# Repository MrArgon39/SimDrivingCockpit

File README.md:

# SimDrivingCockpit
All the code and other assorted stuff for this project

Folder Explanation
<ul>
  <li>Code - All of the code that I have made and will make.</li>
  <li>Reference Images - Mainly used for the steering wheel design.</li>
  <li>Make Physical Things - Where laser files and 3D? printing files will go. Same with PCBs.</li>
<li>Service Documentation - All of the docs about what wire I need to put where to get things to work.</li>
</ul>
Everything contained within the service documentation folder has not been created by me, and belongs to Lexus/Toyota.

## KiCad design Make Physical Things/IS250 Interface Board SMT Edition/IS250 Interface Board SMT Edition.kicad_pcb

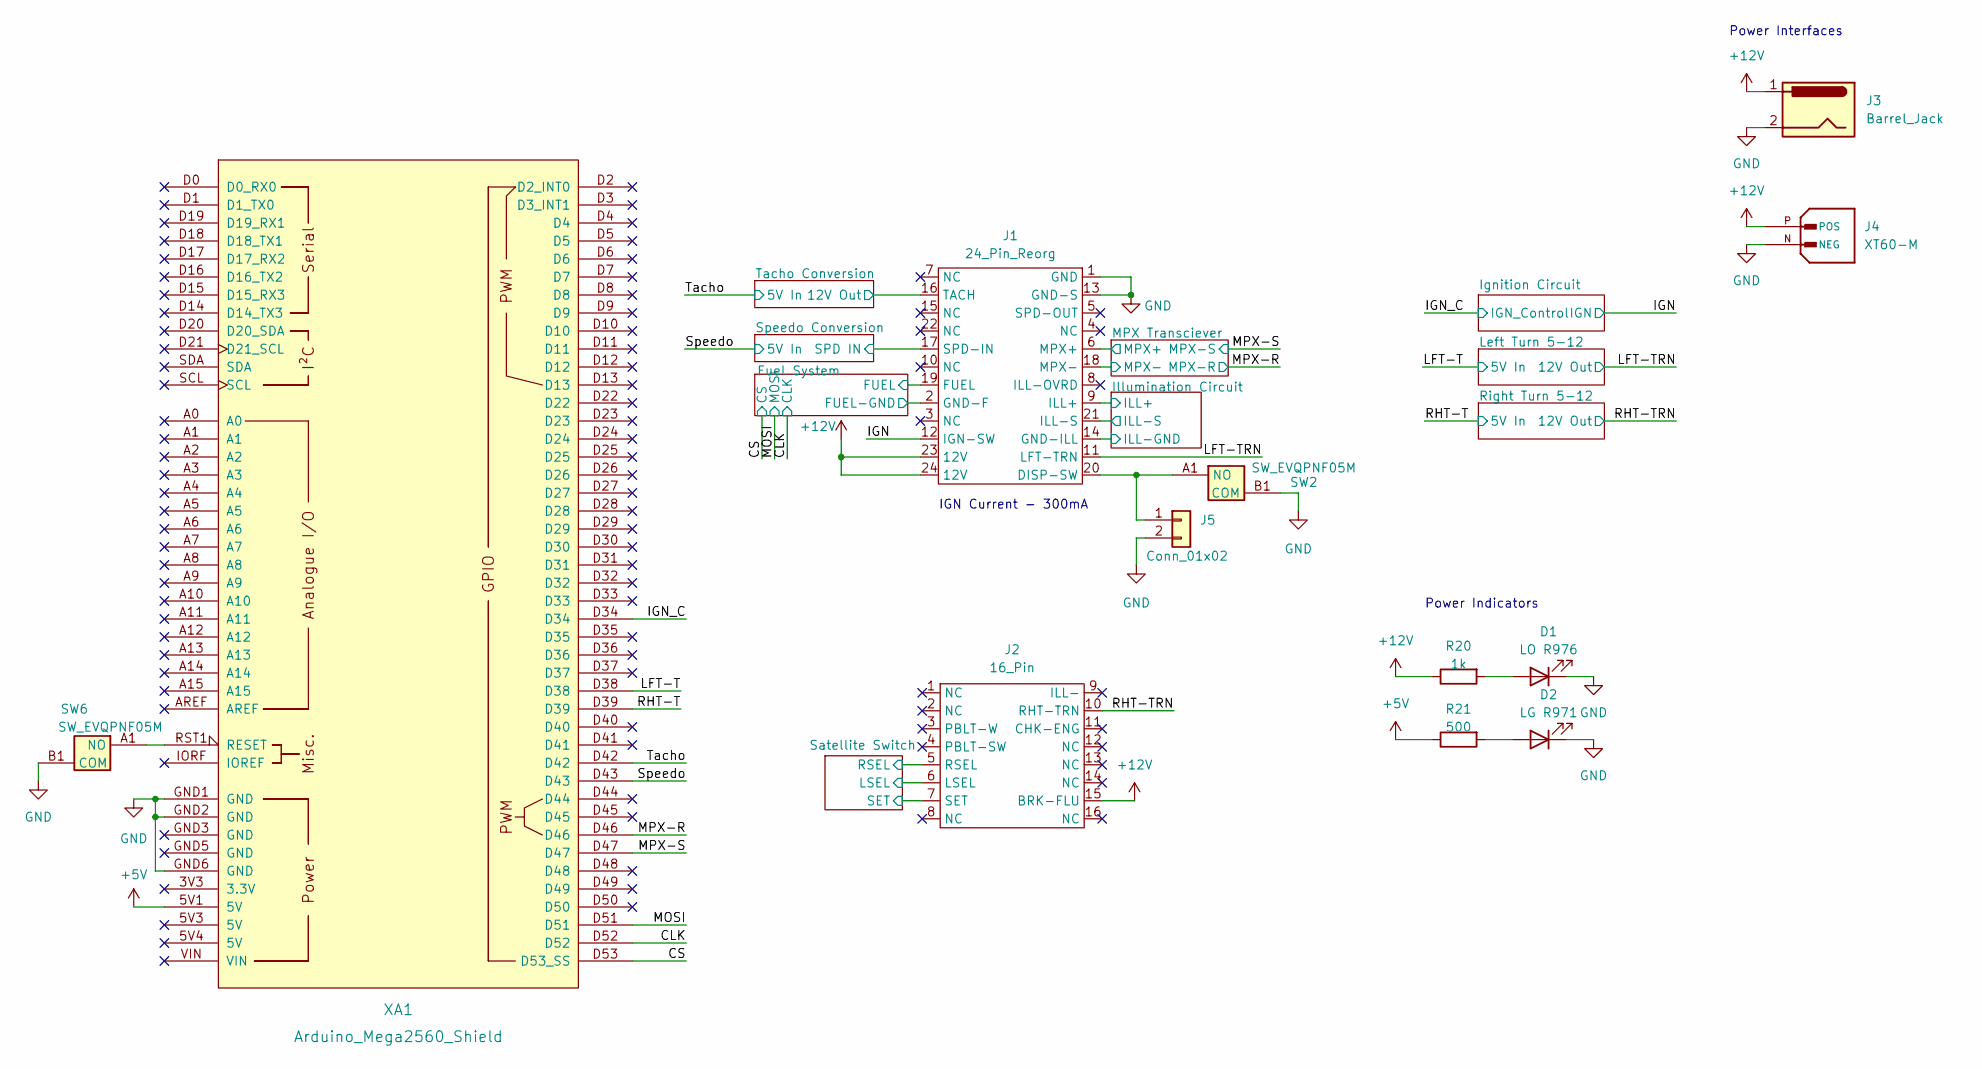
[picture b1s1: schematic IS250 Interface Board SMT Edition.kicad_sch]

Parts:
D1: LO R976; LEDC2012X90N
D2: LG R971; LEDC2012X90N
J1: 24_Pin_Reorg; 24Pin
J2: 16_Pin; 16Pin
J3: Barrel_Jack; BarrelJack_Horizontal
J4: XT60-M; AMASS_XT60-M; PARTREV V1.2
J5: Conn_01x02; PinHeader_1x02_P2.54mm_Vertical
R20: 1k; R_0805_2012Metric_Pad1.20x1.40mm_HandSolder
R21: 500; R_0805_2012Metric_Pad1.20x1.40mm_HandSolder
SW2, SW6: SW_EVQPNF05M; EVQPNF05M; Mouser Part Number 667-EVQ-PNF05M
XA1: Arduino_Mega2560_Shield

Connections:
+5V: R21.1, XA1.5V1 (5V); also elsewhere on the board
/CLK: XA1.D52; also elsewhere on the board
/CS: XA1.D53 (D53_SS); also elsewhere on the board
/Fuel System/FUEL: J1.19 (FUEL); also elsewhere on the board
/Fuel System/FUEL-GND: J1.2 (GND-F); also elsewhere on the board
/IGN: J1.12 (IGN-SW); also elsewhere on the board
/IGN_C: XA1.D34; also elsewhere on the board
/Illumination Circuit/ILL+: J1.9 (ILL+); also elsewhere on the board
/Illumination Circuit/ILL-GND: J1.14 (GND-ILL); also elsewhere on the board
/Illumination Circuit/ILL-S: J1.21 (ILL-S); also elsewhere on the board
/LFT-T: XA1.D38; also elsewhere on the board
/LFT-TRN: J1.11 (LFT-TRN); also elsewhere on the board
/MOSI: XA1.D51; also elsewhere on the board
/MPX Transciever/MPX+: J1.6 (MPX+); also elsewhere on the board
/MPX Transciever/MPX-: J1.18 (MPX-); also elsewhere on the board
/MPX-R: XA1.D46; also elsewhere on the board
/MPX-S: XA1.D47; also elsewhere on the board
/RHT-T: XA1.D39; also elsewhere on the board
/RHT-TRN: J2.10 (RHT-TRN); also elsewhere on the board
/Satellite Switch/LSEL: J2.6 (LSEL); also elsewhere on the board
/Satellite Switch/RSEL: J2.5 (RSEL); also elsewhere on the board
/Satellite Switch/SET: J2.7 (SET); also elsewhere on the board
/Speedo: XA1.D43; also elsewhere on the board
/Speedo Conversion/SPD IN: J1.17 (SPD-IN); also elsewhere on the board
/Tacho Conversion/12V Out: J1.16 (TACH); also elsewhere on the board
GND: D1.1 (K), D2.1 (K), J1.1 (GND), J1.13 (GND-S), J3.2, J4.N (NEG), J5.2, SW2.B1 (COM), SW6.B1 (COM), XA1.GND1 (GND), XA1.GND2 (GND), XA1.GND6 (GND); also elsewhere on the board
unnamed: D1.2 (A), R20.2
unnamed: D2.2 (A), R21.2
unnamed: J1.20 (DISP-SW), J5.1, SW2.A1 (NO)
unnamed 47: SW6.A1 (NO), XA1.RST1 (RESET); also elsewhere on the board

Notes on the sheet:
IGN Current - 300mA
Power Interfaces
Power Indicators

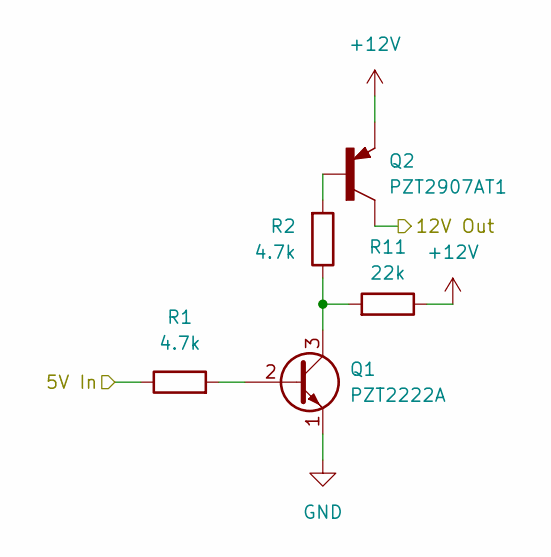
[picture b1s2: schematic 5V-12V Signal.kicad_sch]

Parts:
Q1: PZT2222A; SOT-223
Q2: PZT2907AT1; SOT-223
R1, R2: 4.7k; R_0805_2012Metric_Pad1.20x1.40mm_HandSolder
R11: 22k; R_0805_2012Metric_Pad1.20x1.40mm_HandSolder

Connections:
/Tacho Conversion/12V Out: Q2.3 (C); also elsewhere on the board
GND: Q1.1 (E); also elsewhere on the board
unnamed: Q1.2 (B), R1.2
unnamed: Q2.2 (B), R2.2

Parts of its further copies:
Q8, Q10: PZT2222A; SOT-223
Q9, Q11: PZT2907AT1; SOT-223
R13, R14, R16, R17: 4.7k; R_0805_2012Metric_Pad1.20x1.40mm_HandSolder
R15, R18: 22k; R_0805_2012Metric_Pad1.20x1.40mm_HandSolder

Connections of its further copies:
/LFT-T: R13.1; also elsewhere on the board
/LFT-TRN: Q9.3 (C); also elsewhere on the board
/RHT-T: R16.1; also elsewhere on the board
/RHT-TRN: Q11.3 (C); also elsewhere on the board
GND: Q8.1 (E), Q10.1 (E); also elsewhere on the board
unnamed: Q8.2 (B), R13.2
unnamed: Q8.3 (C), R14.1, R15.2
unnamed: Q9.2 (B), R14.2
unnamed: Q10.2 (B), R16.2
unnamed: Q10.3 (C), R17.1, R18.2
unnamed: Q11.2 (B), R17.2

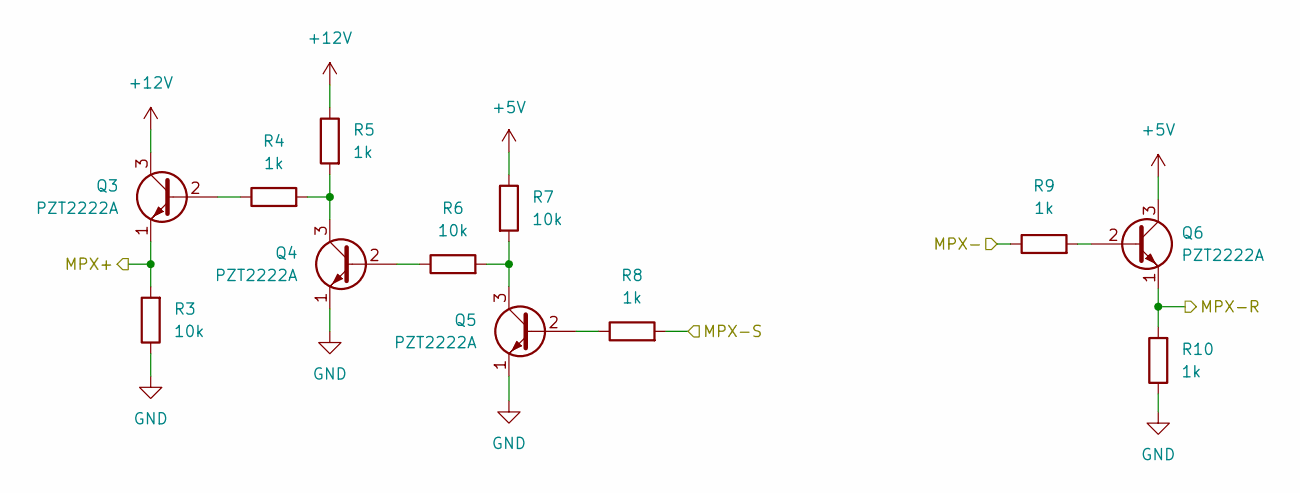
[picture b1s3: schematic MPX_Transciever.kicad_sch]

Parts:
Q3, Q4, Q5, Q6: PZT2222A; SOT-223
R3, R6, R7: 10k; R_0805_2012Metric_Pad1.20x1.40mm_HandSolder
R4, R5, R8, R9, R10: 1k; R_0805_2012Metric_Pad1.20x1.40mm_HandSolder

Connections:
+5V: Q6.3 (C), R7.1; also elsewhere on the board
/MPX Transciever/MPX+: Q3.1 (E), R3.2; also elsewhere on the board
/MPX Transciever/MPX-: R9.1; also elsewhere on the board
/MPX-R: Q6.1 (E), R10.2; also elsewhere on the board
/MPX-S: R8.2; also elsewhere on the board
GND: Q4.1 (E), Q5.1 (E), R3.1, R10.1; also elsewhere on the board
unnamed: Q3.2 (B), R4.1
unnamed: Q4.2 (B), R6.1
unnamed: Q4.3 (C), R4.2, R5.2
unnamed: Q5.2 (B), R8.1
unnamed: Q5.3 (C), R6.2, R7.2
unnamed: Q6.2 (B), R9.2

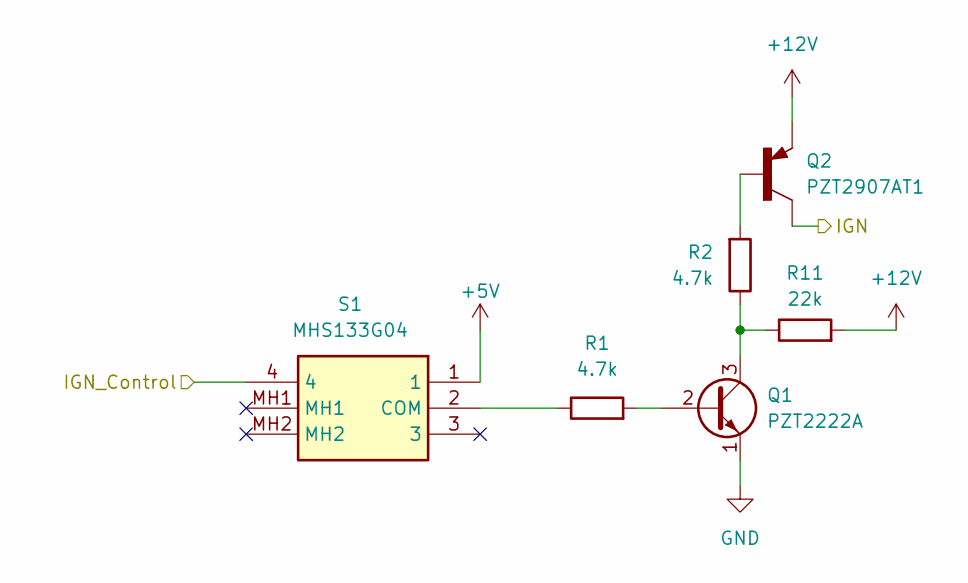
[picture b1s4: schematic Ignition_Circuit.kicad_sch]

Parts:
Q1: PZT2222A; SOT-223
Q2: PZT2907AT1; SOT-223
R1, R2: 4.7k; R_0805_2012Metric_Pad1.20x1.40mm_HandSolder
R11: 22k; R_0805_2012Metric_Pad1.20x1.40mm_HandSolder
S1: MHS133G04; Mouser Part Number 506-MHS133G04

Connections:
+5V: S1.1; also elsewhere on the board
/IGN_C: S1.4; also elsewhere on the board
/Tacho Conversion/12V Out: Q2.3 (C); also elsewhere on the board
GND: Q1.1 (E); also elsewhere on the board
unnamed: Q1.2 (B), R1.2
unnamed: Q2.2 (B), R2.2

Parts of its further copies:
Q8, Q10, Q12: PZT2222A; SOT-223
Q9, Q11, Q13: PZT2907AT1; SOT-223
R13, R14, R16, R17, R22, R23: 4.7k; R_0805_2012Metric_Pad1.20x1.40mm_HandSolder
R15, R18, R24: 22k; R_0805_2012Metric_Pad1.20x1.40mm_HandSolder

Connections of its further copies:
/IGN: Q13.3 (C); also elsewhere on the board
/LFT-T: R13.1; also elsewhere on the board
/LFT-TRN: Q9.3 (C); also elsewhere on the board
/RHT-T: R16.1; also elsewhere on the board
/RHT-TRN: Q11.3 (C); also elsewhere on the board
GND: Q8.1 (E), Q10.1 (E), Q12.1 (E); also elsewhere on the board
unnamed: Q8.2 (B), R13.2
unnamed: Q8.3 (C), R14.1, R15.2
unnamed: Q9.2 (B), R14.2
unnamed: Q10.2 (B), R16.2
unnamed: Q10.3 (C), R17.1, R18.2
unnamed: Q11.2 (B), R17.2
unnamed: Q12.2 (B), R22.2
unnamed: Q12.3 (C), R23.1, R24.1
unnamed: Q13.2 (B), R23.2

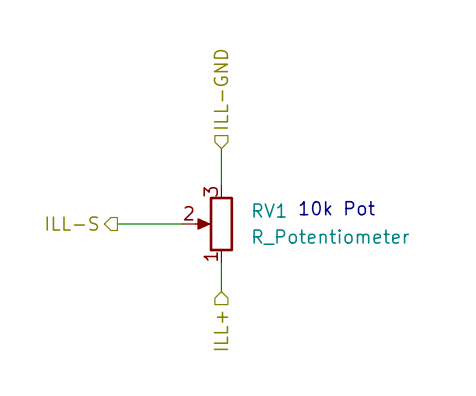
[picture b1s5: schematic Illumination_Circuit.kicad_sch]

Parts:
RV1: R_Potentiometer; Potentiometer_Bourns_3386P_Vertical

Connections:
/Illumination Circuit/ILL+: RV1.1; also elsewhere on the board
/Illumination Circuit/ILL-GND: RV1.3; also elsewhere on the board
/Illumination Circuit/ILL-S: RV1.2; also elsewhere on the board

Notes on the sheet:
10k Pot

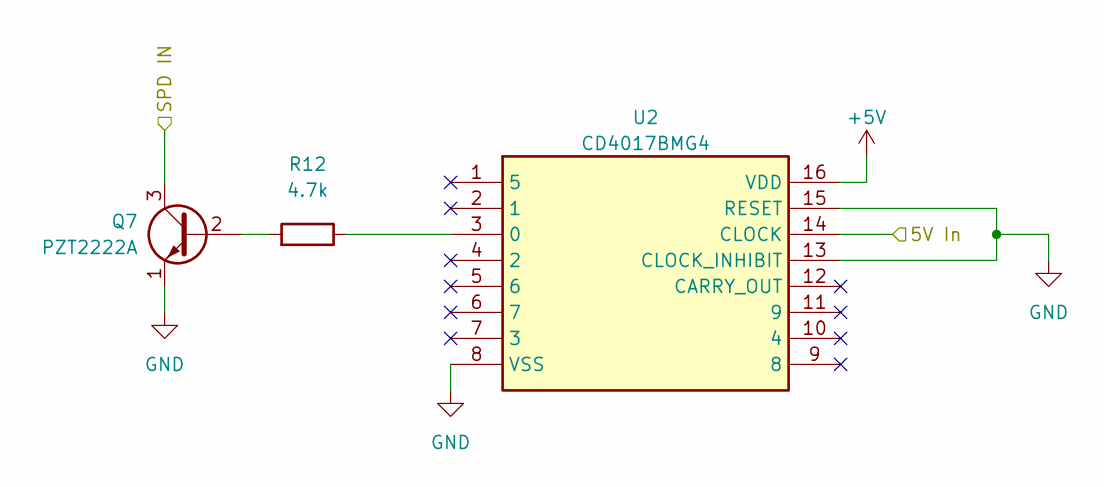
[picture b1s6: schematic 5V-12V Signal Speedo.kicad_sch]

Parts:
Q7: PZT2222A; SOT-223
R12: 4.7k; R_0805_2012Metric_Pad1.20x1.40mm_HandSolder
U2: CD4017BMG4; SOIC127P600X175-16N; Mouser Part Number 595-CD4017BMG4

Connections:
+5V: U2.16 (VDD); also elsewhere on the board
/Speedo: U2.14 (CLOCK); also elsewhere on the board
/Speedo Conversion/SPD IN: Q7.3 (C); also elsewhere on the board
GND: Q7.1 (E), U2.8 (VSS), U2.13 (CLOCK_INHIBIT), U2.15 (RESET); also elsewhere on the board
unnamed: Q7.2 (B), R12.2
unnamed: R12.1, U2.3 (0)

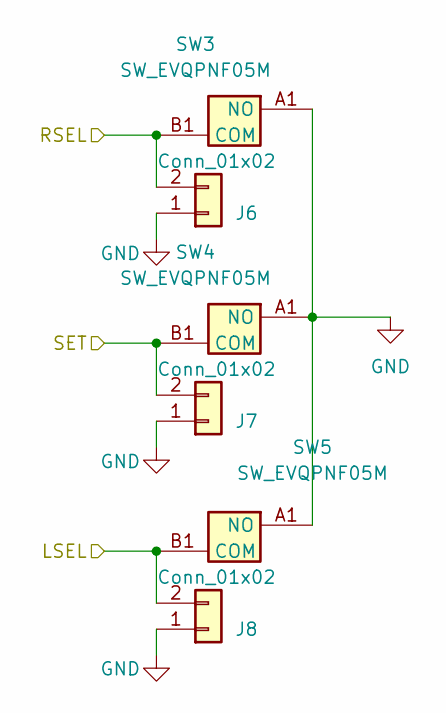
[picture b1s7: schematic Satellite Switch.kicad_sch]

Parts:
J6, J7, J8: Conn_01x02; PinHeader_1x02_P2.54mm_Vertical
SW3, SW4, SW5: SW_EVQPNF05M; EVQPNF05M; Mouser Part Number 667-EVQ-PNF05M

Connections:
/Satellite Switch/LSEL: J8.2, SW5.B1 (COM); also elsewhere on the board
/Satellite Switch/RSEL: J6.2, SW3.B1 (COM); also elsewhere on the board
/Satellite Switch/SET: J7.2, SW4.B1 (COM); also elsewhere on the board
GND: J6.1, J7.1, J8.1, SW3.A1 (NO), SW4.A1 (NO), SW5.A1 (NO); also elsewhere on the board

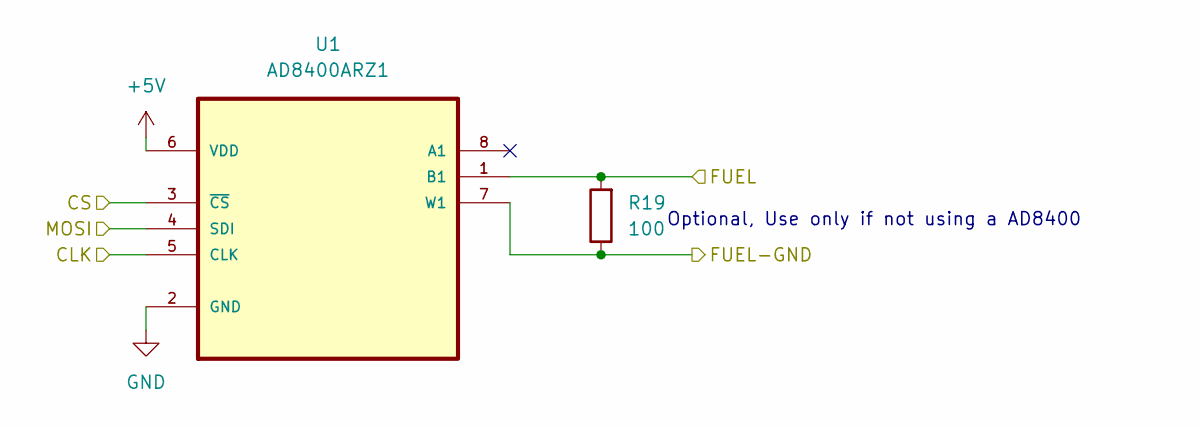
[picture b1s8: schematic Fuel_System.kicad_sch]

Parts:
R19: 100; R_0805_2012Metric_Pad1.20x1.40mm_HandSolder
U1: AD8400ARZ1; SO-8_3.9x4.9mm_P1.27mm; MPN AD8400ARZ1

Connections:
+5V: U1.6 (VDD); also elsewhere on the board
/CLK: U1.5 (CLK); also elsewhere on the board
/CS: U1.3 (~CS); also elsewhere on the board
/Fuel System/FUEL: R19.2, U1.1 (B1); also elsewhere on the board
/Fuel System/FUEL-GND: R19.1, U1.7 (W1); also elsewhere on the board
/MOSI: U1.4 (SDI); also elsewhere on the board
GND: U1.2 (GND); also elsewhere on the board

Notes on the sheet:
Optional, Use only if not using a AD8400

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
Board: 2 copper layers, 57 parts (12 on the bottom side), 53 nets, no tracks yet.

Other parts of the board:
locked: SW_EVQPNF05M; EVQPNF05M

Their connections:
GND: locked.B1 (COM); also elsewhere on the board
unnamed 47: locked.A1 (NO); also elsewhere on the board

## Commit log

2022-09-04 Added fundamental things to the repo
    Added all of my code up to this point, as well as the reference that I am using for the physical wheel.
    The pertinent parts of the service documentation have also been added for easy reference.
2022-09-04 Changed file locations
2022-09-05 Added the rest of the D-Pad controls for the wheel
2022-09-05 Added Cruise Control Buttons
2022-09-05 Added pedals, changed designators, moved buttons
2022-09-07 Added test code for the Speedometer, which works
2022-09-07 Edited Speed Test to work with SimHub
2022-09-08 Copied SHCP, Working Speedo Prototype
2022-09-08 gitignore broken
2022-09-08 Added the modified version of the BeanMPX lib
2022-09-08 Added BeanMPX library modified to use Timer3
2022-09-08 Experimented with speed, will rewrite for a 4017IC
2022-09-08 Majority of MPX Communications work
2022-09-11 Add the test code for the fuel gauge
    Added test code to implement the AD8400 digipot to control the fuel gauge
2022-09-11 Adapted fuel code to test on a Mega
2022-09-11 Added fuel code, and redid light and cruise code
2022-09-15 Updated Pedals to work correctly
2022-09-16 Implemented temp gauge, and added cruise speed
2022-09-17 Implemented cruise speed properly
2022-09-19 Redid HID reports to reduce report numbers
2022-09-20 Added Turn Signals
2022-09-23 Changed button check to allow multiple at once
2022-09-23 Added Paddles and missing back button
2022-10-20 Added Schematic
    Added the KiCAD Schematic for the Interface board
2022-10-20 Added Plate Detection Functionality
    Added the ability for the Pico to detect which faceplate is installed, and adjust the calibration accordingly
2022-10-20 Updated Components to have footprints
    Added footprints to components that had the wrong ones or were completely missing
2022-10-24 Added components to PCB
    Got all the components adding onto the PCB, and fixed pinname errors with the 2907
2022-10-24 Added XT60 and backup fuel resistor
    Added an XT60 power connector, and an optional resistor if there isn't an AD8400 connected, so that the fuel gauge will show not empty
2022-10-25 Added Reset Circuit
    Added a button to allow you to reset the arduino, if it decides to die. Also fixed the footprints for the buttons so that they actually function as buttons.
2022-10-25 Added Power LED's and PCB foundation
    Added LED's to indicate both 12v and 5v power to the board, and begun work on the PCB
2022-10-27 More PCB Layout
    PCB laid out further, and just requires routing and silkscreen.
2022-10-27 PCB Layout Finalised
    Finalised the layout, routing and silkscreen still to be completed.
2022-10-27 PCB routing and Test Points
    The routing for the PCB is complete, and I have added test points for the waveforms
2022-10-27 Finalised Layout and Silkscreen
    Finished all of the PCB design, added the test points and silkscreen.
2022-10-31 Added mounting holes
    Added M3 Holes for standoffs, for mounting in an enclosure or to keep it off a desk
2022-10-31 Fixed Error
    Updated footprints for custom objects with correct hole sizing, and fixed routing errors caused by the change.
2022-10-31 Create MPX Codes
    Added the dictionary for the MPX codes that make the cluster do stuff, whether useful to the project or not
2022-10-31 Added Current Gear
2022-10-31 Updated Silkscreen
    Fixed the silkscreen for the arduino socket
2022-11-01 Updated Silkscreen
    Added resistor values to the silkscreen
2022-11-01 Updated analog functions
2022-11-03 Comments, many Comments
2022-11-08 Fixed Service Documentation
    Replaced HTML docs with working PDF versions
2022-11-14 Added HTML BOM
    Added the HTML BOM to the repo, so that I can link to it.
2023-10-07 Added Some Shit
    Some shit was added
2024-07-28 Made some updates idk
